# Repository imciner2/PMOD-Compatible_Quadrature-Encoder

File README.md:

# PMOD-Compatible_Quadrature-Encoder
Circuit board to interface a 5-pin DIN quadrature encoder to a PMOD port.

## Library Housekeeping

### To read in any changes from the Kicad library repository to this one:

1. Fetch the changes

    ``` git fetch libraries ```

2. Merge the changes

    ``` git merge -s subtree --squash libraries/master ```

3. Commit the changes

    ``` git commit -m "Updated libraries directory" ```

### To push any of the changes from this project to the Kicad libarary repository

1. Create commits for the changes (make them seperate from everything else)

2. Create a new branch locally

    ``` git checkout -b library-work libraries/master ```

3. Select the commits to add to the library (The command shown below will use the 5th commit before the current revision, simply modify the 5 to change which commit is referenced)

    ``` git cherry-pick -x --strategy=subtree master~5 ```

4. Push the new changes back to the libraries repository

    ``` git push libraries library-work:master ```

5. Go back to the working repository

    ``` git checkout master ```

6. Delete the branch you just used

    ``` git branch -D library-work ```

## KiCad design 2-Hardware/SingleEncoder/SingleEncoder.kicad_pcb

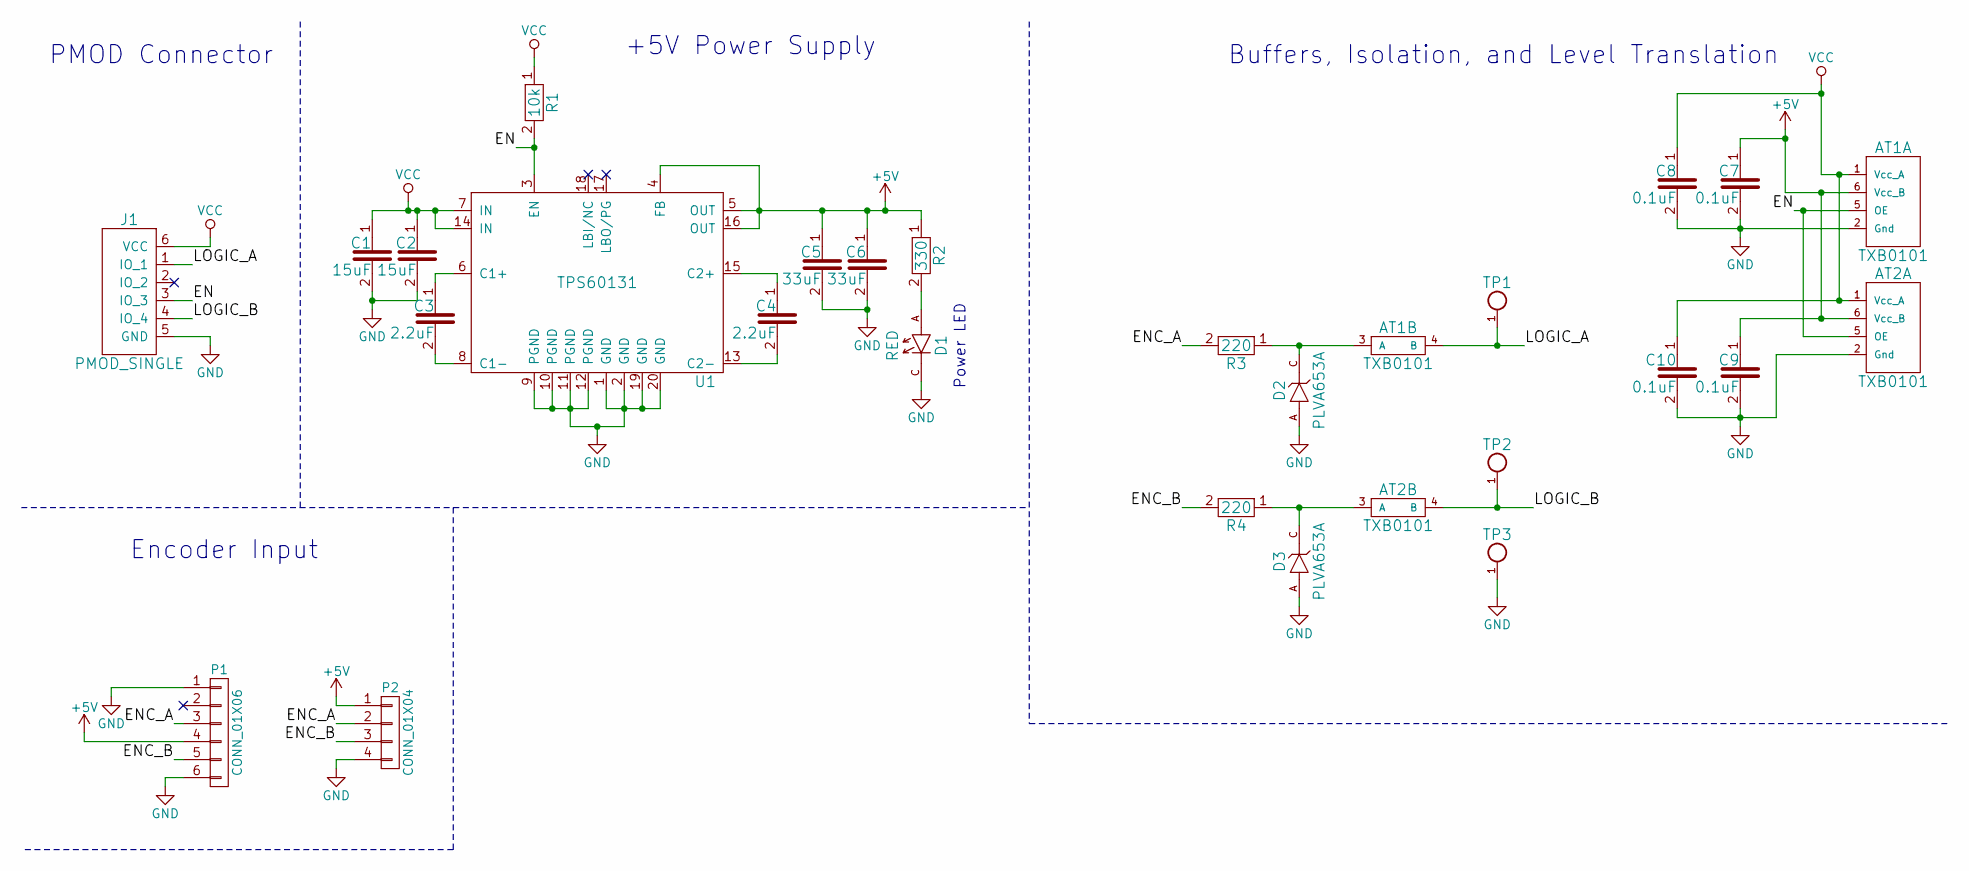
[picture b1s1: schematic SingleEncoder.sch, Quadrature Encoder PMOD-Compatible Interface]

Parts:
AT1, AT2: TXB0101; SOT-23-6; DigikeyNumber 296-21664-1-ND
C1, C2: 15uF; SMD_0805; DigikeyNumber 445-14362-1-ND
C3, C4: 2.2uF; SMD_0805; DigikeyNumber 445-1588-1-ND
C5, C6: 33uF; SMD_0805; DigikeyNumber 445-8238-1-ND
C7, C8, C9, C10: 0.1uF; SMD_0805; DigikeyNumber 311-1141-1-ND
D1: RED; LED_1206; DigikeyNumber 754-1137-1-ND
D2, D3: PLVA653A; DIODE_SOT-23-3; DigikeyNumber 568-6472-1-ND
J1: PMOD_SINGLE; PMOD_SINGLE_MALE; DigikeyNumber 609-3313-ND
P1: CONN_01X06; DIN_CUI_SDS-50J; DigikeyNumber CP-2350-ND
P2: CONN_01X04; CONN_2.54mm_1x4
R1: 10k; SMD_0805; DigikeyNumber P10.0KCCT-ND
R2: 330; SMD_0805; DigikeyNumber P330CCT-ND
R3, R4: 220; SMD_0805; DigikeyNumber P220CCT-ND
TP1, TP2: TEST_POINT; TESTPOINT_063; DigikeyNumber 36-5013-ND
TP3: TEST_POINT; TESTPOINT_063; DigikeyNumber 36-5011-ND
U1: TPS60131; SSOP_20_4.5mm_6.6mm_0.65mm_PWP; DigikeyNumber 296-2272-5-ND

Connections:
+5V: AT1.6 (Vcc_B), AT2.6 (Vcc_B), C5.1, C6.1, C7.1, C9.1, P1.4, P2.1, R2.1, U1.4 (FB), U1.5 (OUT), U1.16 (OUT)
/EN: AT1.5 (OE), AT2.5 (OE), J1.3 (IO_3), R1.2, U1.3 (EN)
/ENC_A: P1.3, P2.2, R3.2
/ENC_B: P1.5, P2.3, R4.2
/LOGIC_A: AT1.4 (B), J1.1 (IO_1), TP1.1
/LOGIC_B: AT2.4 (B), J1.4 (IO_4), TP2.1
GND: AT1.2 (Gnd), AT2.2 (Gnd), C1.2, C2.2, C5.2, C6.2, C7.2, C8.2, C9.2, C10.2, D1.C, D2.A, D3.A, J1.5 (GND), P1.1, P1.6, P2.4, TP3.1, U1.1 (GND), U1.2 (GND), U1.9 (PGND), U1.10 (PGND), U1.11 (PGND), U1.12 (PGND), U1.19 (GND), U1.20 (GND)
unnamed: AT1.3 (A), D2.C, R3.1
unnamed: AT2.3 (A), D3.C, R4.1
unnamed: C3.1, U1.6 (C1+)
unnamed: C3.2, U1.8 (C1-)
unnamed: C4.1, U1.15 (C2+)
unnamed: C4.2, U1.13 (C2-)
unnamed: D1.A, R2.2
VCC: AT1.1 (Vcc_A), AT2.1 (Vcc_A), C1.1, C2.1, C8.1, C10.1, J1.6 (VCC), R1.1, U1.7 (IN), U1.14 (IN)

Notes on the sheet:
PMOD Connector
+5V Power Supply
Encoder Input
Buffers, Isolation, and Level Translation
Power LED

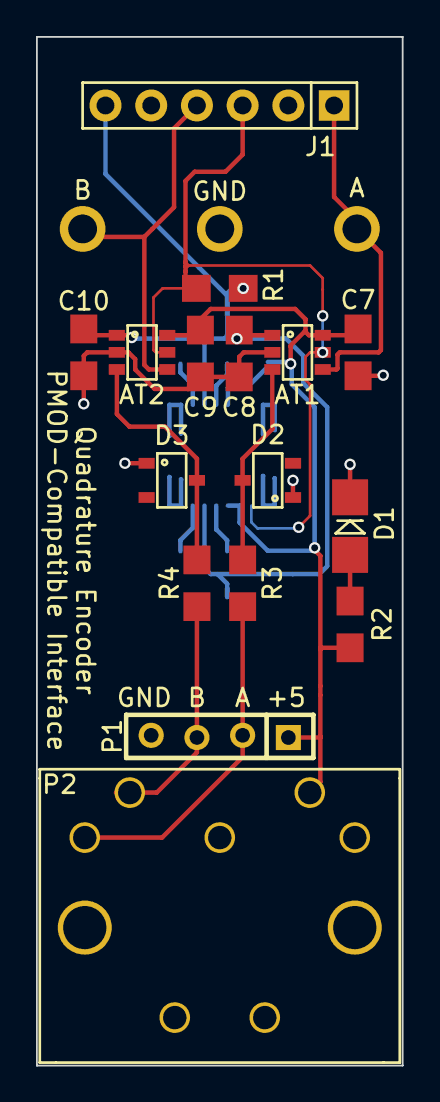
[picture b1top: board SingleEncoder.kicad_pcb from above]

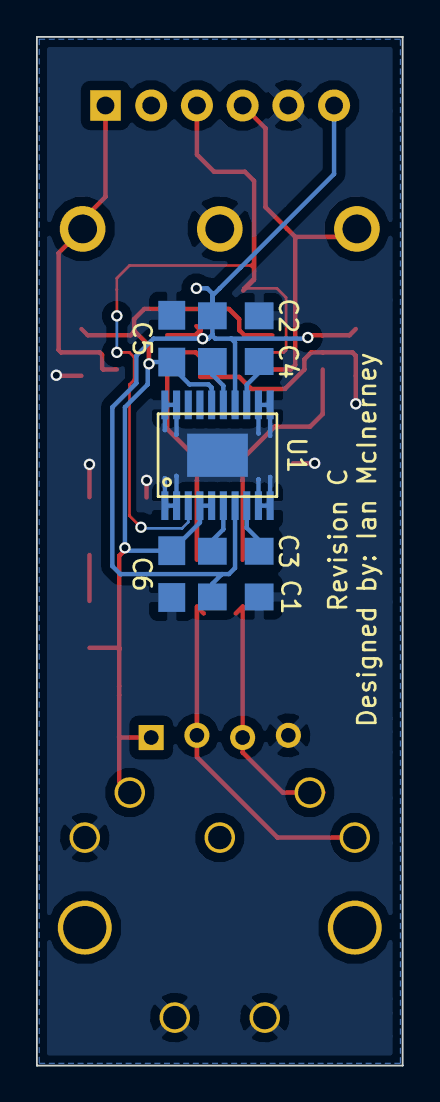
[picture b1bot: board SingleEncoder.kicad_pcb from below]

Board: 2 copper layers, 20.3 x 57.2 mm, 26 parts (7 on the bottom side), 15 nets.

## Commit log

2015-07-10 Kicad libraries initial commit
2015-07-10 Part datasheets
2015-07-10 Updated library directory
2015-07-14 Added component datasheets
2015-07-14 Added PMOD schematic symbols
2015-07-14 Added NPN and PNP schematic symbols
2015-07-14 Added TI charge pump devices
2015-07-14 Created new library for amplifier ICs
2015-07-14 Added test point, optocoupler
2015-07-14 Schematic for single encoder PMOD
2015-07-15 Updated readme with library stuff
2015-07-15 Fixed issue with diode footprint file
2015-07-15 PMOD-Compatible connector footprints
2015-07-15 Footprint for a CUI SDS-50J DIN Connector
2015-07-15 Footprint for a testpoint
2015-07-15 Started footprint association
2015-07-15 Pulled in most recent library changes
2015-07-15 Updated libraries directory
2015-07-16 Added 3D model to PMODs
2015-07-16 Added 3D models for DIN connectors
2015-07-16 Associated DIN footprint
2015-07-16 Renamed SOIC and SSOP packages
2015-07-16 Finished footprint association
2015-07-17 Fixed pin numbering issue
2015-07-17 Started circuit board layout
2015-07-17 Fixed annular ring issue
2015-07-17 Finalized BOM
2015-07-17 Board production files
2015-07-17 Completed single encoder files
2015-07-17 Removed backup file
2015-07-17 Added git ignore file
2015-08-03 Added 4-pin connector behind the DIN connector
2015-08-03 Updated final production files
2017-01-08 Removed libraries directory
2017-01-08 Changed over to submodule for library
2017-01-22 Replaced Opto-isolator with I2C level shifter
2017-01-22 Changed level translator
2017-01-23 Associated footprints, reimported to board. Layout not done.
2017-07-26 Updated libraries to recent version
2017-07-26 Updated board layout to use level shifter
2017-07-26 Updated PMOD connector holes
2017-10-09 Updated isolation circuit
    - Swapped TXB0102 for 2 TXB0101
    - Re-did board layout to accomodate new parts
2017-10-10 Revised layout and created BOM
2017-10-10 Updated production files with Rev C part
2017-10-11 Update BOM to make sure all parts are in stock.
